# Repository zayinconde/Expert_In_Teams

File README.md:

This is my expert and teams electronics repository. The project is a multi-dsiciplinary project. This repository contains all the files related to the electronics part by me (Zayin Conde). 

The embedded software is developed in VS code using platformio cross platform developemnt tool. 

The repository also contains the KICAD files for circuit schematics and PCB designs. 

Additionally, a project B.O.M list is linked along with a brainstorming document (note: language can be informal, used for personal brainstorming and decision making) (View only with SDU Mail)

[📄 View the live Brainstorming Document (Word)](https://syddanskuni.sharepoint.com/:w:/s/AIDeputyExpertinTeams/ETyJX5G7IEFBnaOn01ZgCaMBbD81jJfqN7rkElq9ijI7jw?e=0cWUlB)
[📊 View the live B.O.M list (Excel)](https://syddanskuni.sharepoint.com/:x:/s/AIDeputyExpertinTeams/EaCTvVSukcdOoP5wCQjI0uoB_z5LuD4u5wMGKWqrb4GMKw?e=0rVpbN)

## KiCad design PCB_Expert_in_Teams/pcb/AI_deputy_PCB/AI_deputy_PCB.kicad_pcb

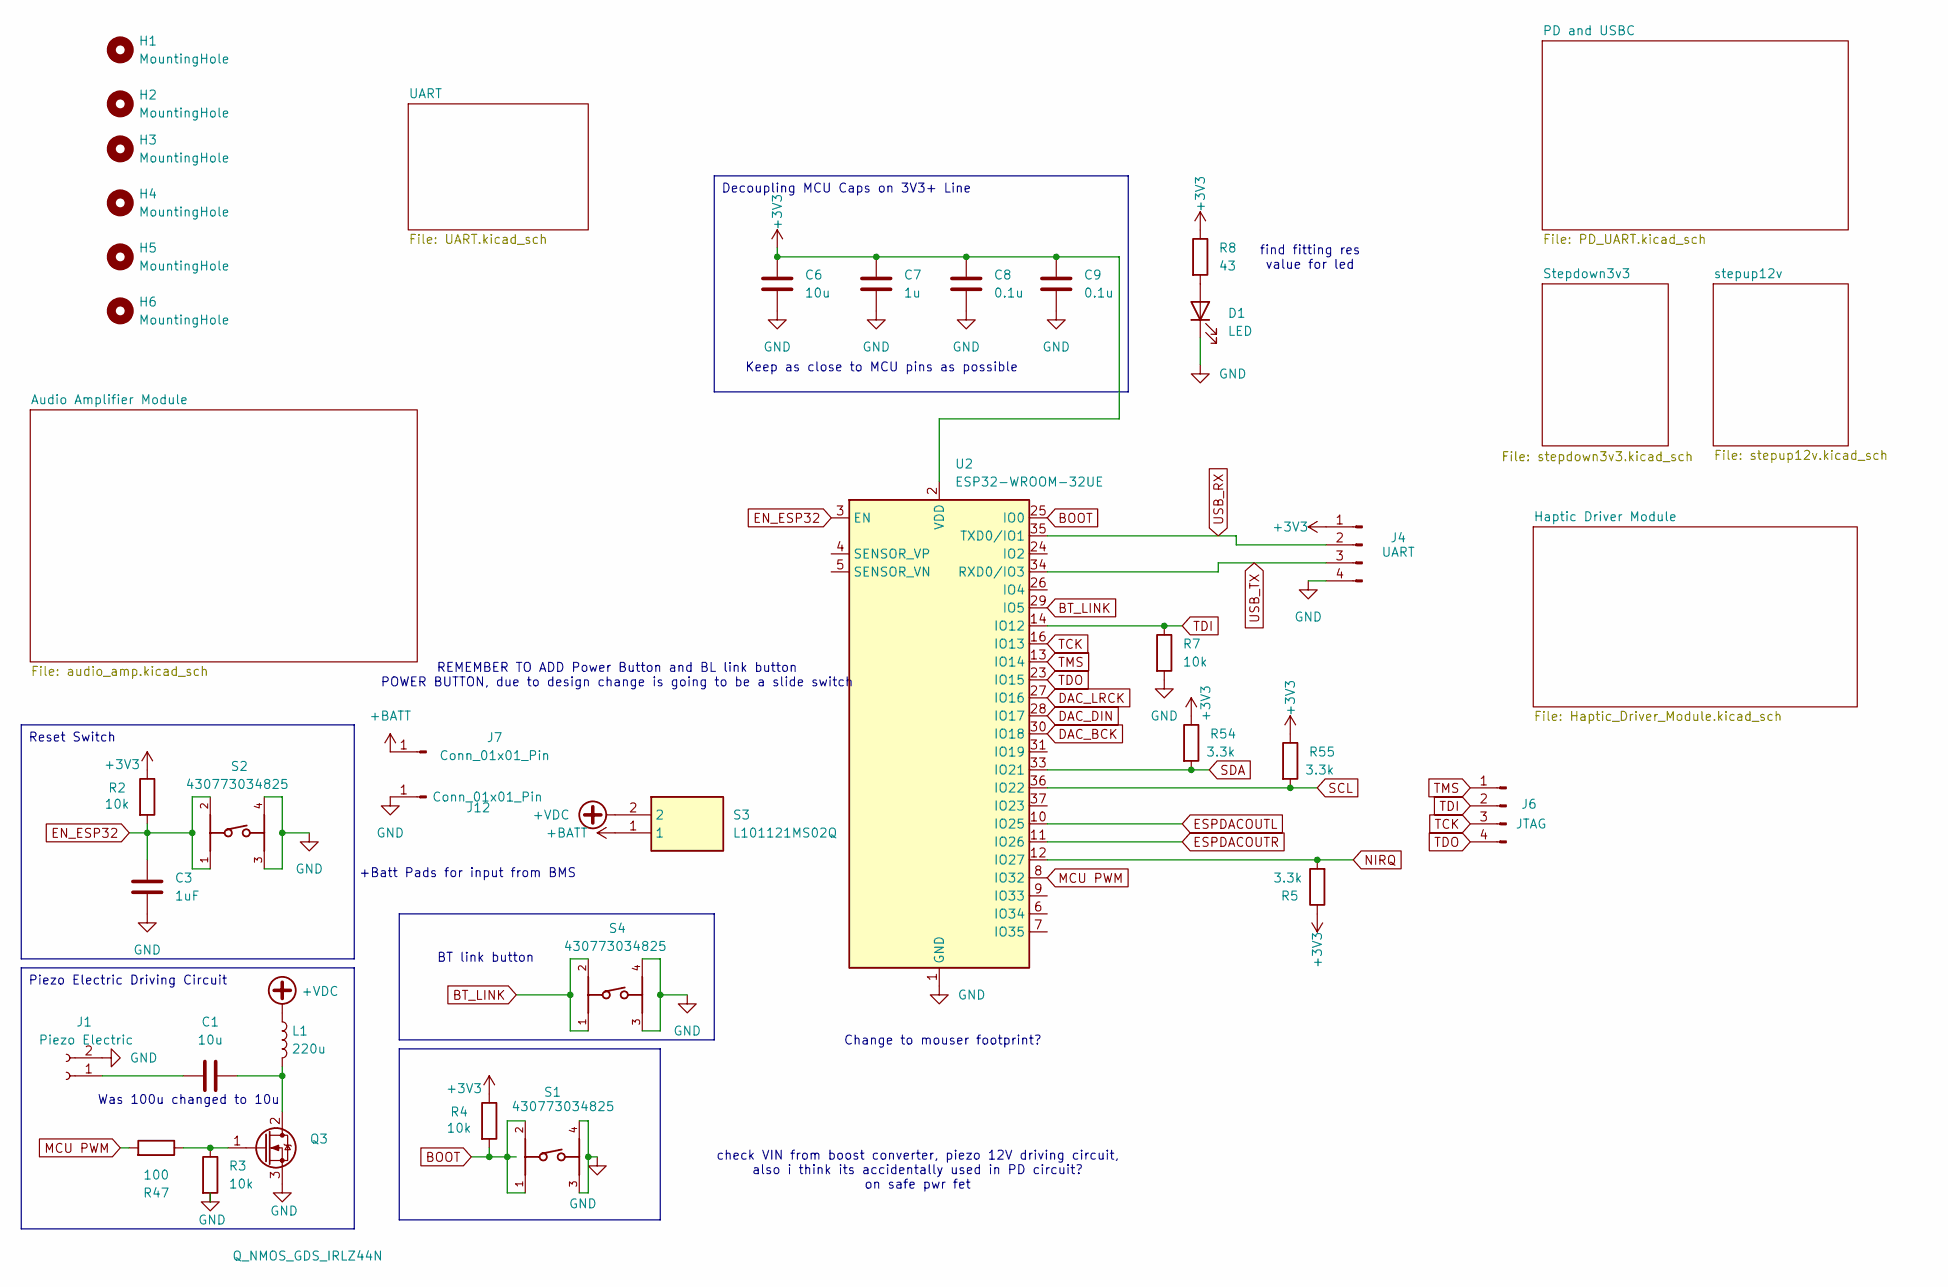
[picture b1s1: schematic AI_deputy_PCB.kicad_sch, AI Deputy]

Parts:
C1, C6: 10u; C_0805_2012Metric_Pad1.18x1.45mm_HandSolder
C3: 1uF; C_0805_2012Metric_Pad1.18x1.45mm_HandSolder
C7: 1u; C_0805_2012Metric_Pad1.18x1.45mm_HandSolder
C8, C9: 0.1u; C_0805_2012Metric_Pad1.18x1.45mm_HandSolder
D1: LED; LED_0805_2012Metric_Pad1.15x1.40mm_HandSolder
H1, H2, H3, H4, H5, H6: MountingHole; MountingHole_3mm
J1: Piezo Electric; JST_XH_S2B-XH-A-1_1x02_P2.50mm_Horizontal
J4: UART; PinHeader_1x04_P2.54mm_Vertical
J6: JTAG; PinHeader_1x04_P2.54mm_Vertical
J7, J12: Conn_01x01_Pin; TestPoint_Pad_4.0x4.0mm
L1: 220u; L_Wuerth_WE-PD-Typ-LS
Q3: Q_NMOS_GDS_IRLZ44N; TO-220-3_Horizontal_TabDown
R2, R3, R4, R7: 10k; R_0805_2012Metric_Pad1.20x1.40mm_HandSolder
R5, R54, R55: 3.3k; R_0805_2012Metric_Pad1.20x1.40mm_HandSolder
R8: 43; R_0805_2012Metric_Pad1.20x1.40mm_HandSolder
R47: 100; R_0805_2012Metric_Pad1.20x1.40mm_HandSolder
S1, S2, S4: 430773034825
S3: L101121MS02Q; PWR_SW_L101021MS02Q; Mouser Part Number 611-L101121MS02Q
U2: ESP32-WROOM-32UE

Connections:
+3V3: C6.1, C7.1, C8.1, C9.2, J4.1, R2.1, R4.1, R5.1, R8.1, R54.1, R55.1, U2.2 (VDD); also elsewhere on the board
+BATT: J7.1, S3.1
+VDC: L1.1, S3.2; also elsewhere on the board
BOOT: R4.2, S1.1, S1.2, U2.25 (IO0)
BT_LINK: S4.1, S4.2, U2.29 (IO5)
DAC_BCK: U2.30 (IO18); also elsewhere on the board
DAC_DIN: U2.28 (IO17); also elsewhere on the board
DAC_LRCK: U2.27 (IO16); also elsewhere on the board
EN_ESP32: C3.1, R2.2, S2.1, S2.2, U2.3 (EN)
ESPDACOUTL: U2.10 (IO25); also elsewhere on the board
ESPDACOUTR: U2.11 (IO26); also elsewhere on the board
GND: C3.2, C6.2, C7.2, C8.2, C9.1, D1.1 (K), J1.2, J4.4, J12.1, Q3.3 (S), R3.2, R7.2, S1.3, S1.4, S2.3, S2.4, S4.3, S4.4, U2.1 (GND), U2.15 (GND), U2.38 (GND), U2.39 (GND); also elsewhere on the board
MCU PWM: R47.2, U2.8 (IO32)
NIRQ: R5.2, U2.12 (IO27); also elsewhere on the board
unnamed: D1.2 (A), R8.2
unnamed: C1.1, J1.1
unnamed: C1.2, L1.2, Q3.2 (D)
unnamed: Q3.1 (G), R3.1, R47.1
SCL: R55.2, U2.36 (IO22); also elsewhere on the board
SDA: R54.2, U2.33 (IO21); also elsewhere on the board
TCK: J6.3, U2.16 (IO13)
TDI: J6.2, R7.1, U2.14 (IO12)
TDO: J6.4, U2.23 (IO15)
TMS: J6.1, U2.13 (IO14)
USB_RX: J4.2, U2.35 (TXD0/IO1); also elsewhere on the board
USB_TX: J4.3, U2.34 (RXD0/IO3); also elsewhere on the board

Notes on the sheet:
Keep as close to MCU pins as possible
Was 100u changed to 10u
BT link button
REMEMBER TO ADD Power Button and BL link button POWER BUTTON, due to design change is going to be a slide switch
+Batt Pads for input from BMS
find fitting res value for led
check VIN from boost converter, piezo 12V driving circuit, also i think its accidentally used in PD circuit? on safe pwr fet
Change to mouser footprint?
Piezo Electric Driving Circuit
Decoupling MCU Caps on 3V3+ Line
Reset Switch

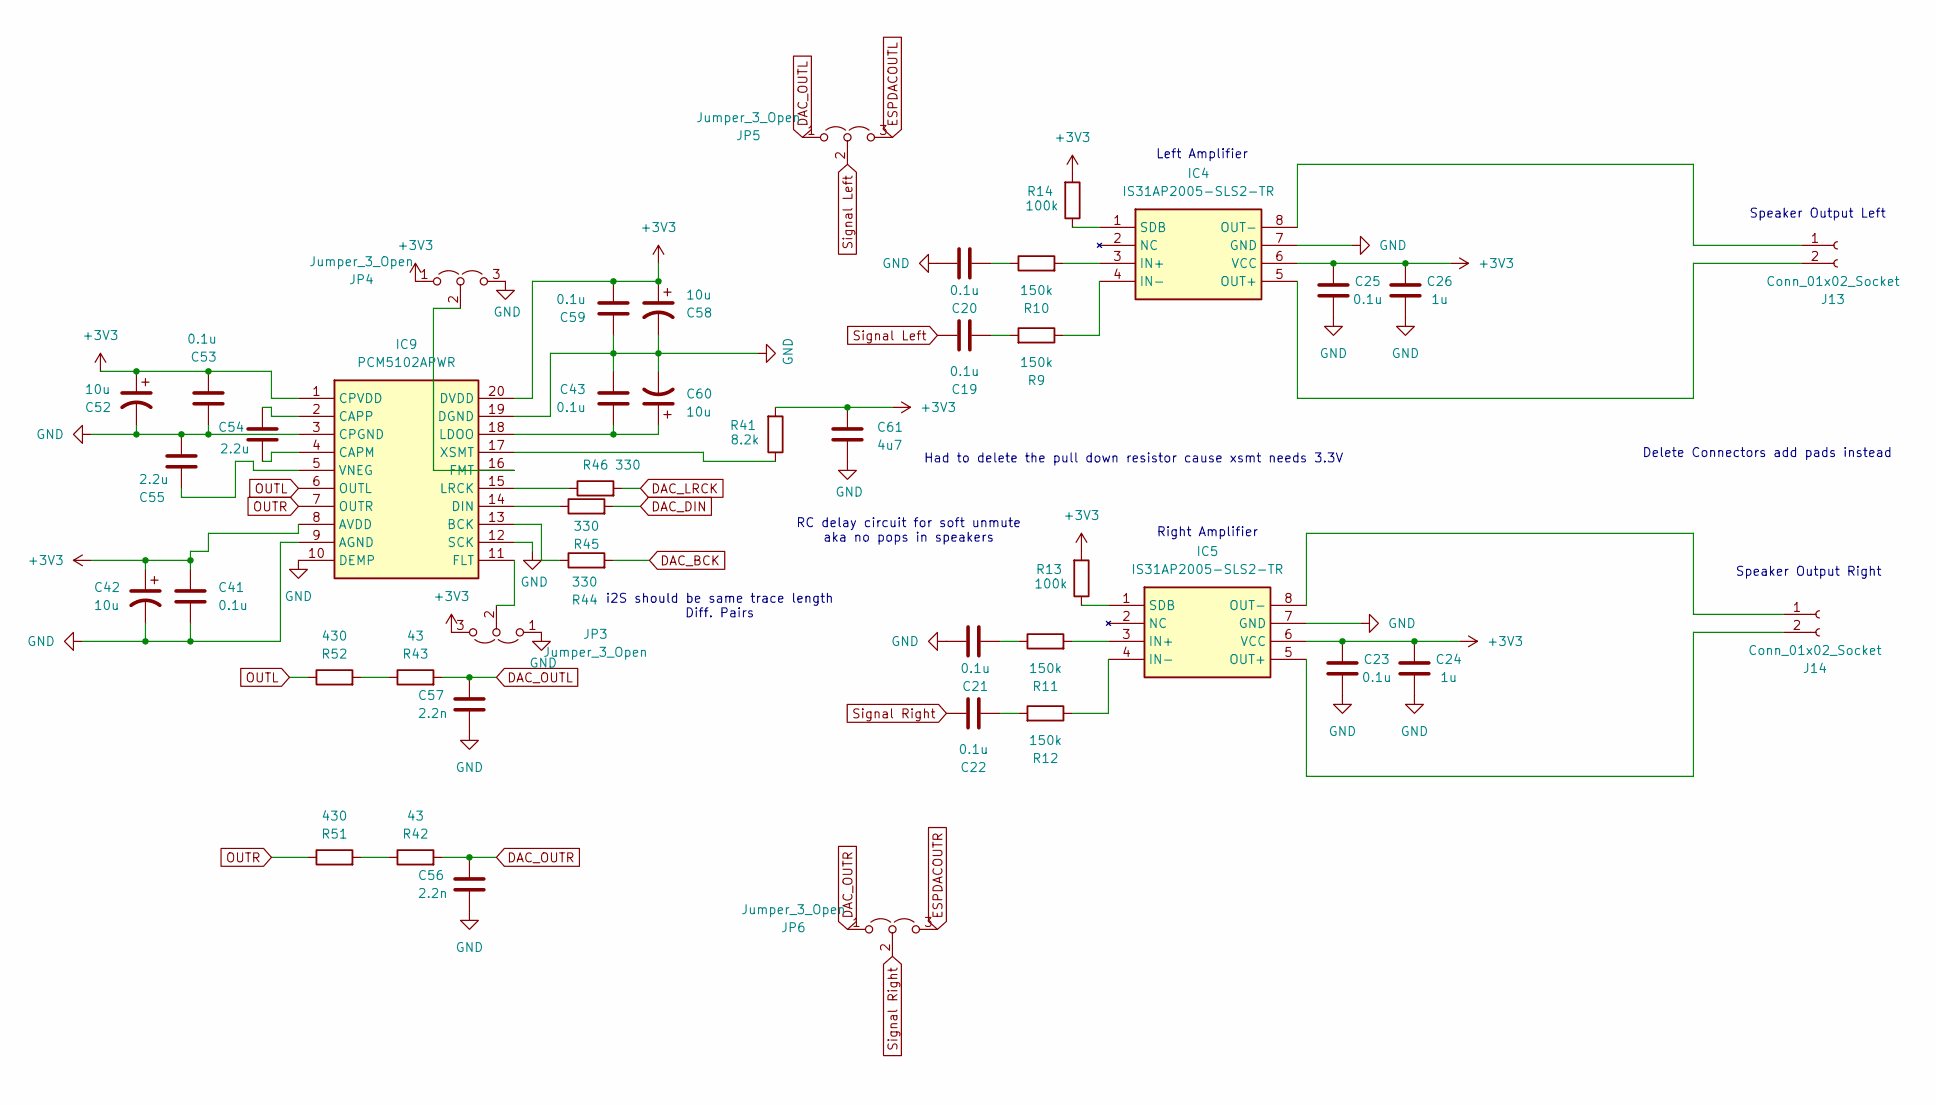
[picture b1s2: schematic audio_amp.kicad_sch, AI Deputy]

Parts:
C19, C20, C21, C22, C23, C25, C41, C43, C53, C59: 0.1u; C_0805_2012Metric_Pad1.18x1.45mm_HandSolder
C24, C26: 1u; C_0805_2012Metric_Pad1.18x1.45mm_HandSolder
C42, C52, C58, C60: 10u; CP_Elec_4x5.4
C54, C55: 2.2u; C_0805_2012Metric_Pad1.18x1.45mm_HandSolder
C56, C57: 2.2n; C_0201_0603Metric_Pad0.64x0.40mm_HandSolder
C61: 4u7; C_0805_2012Metric_Pad1.18x1.45mm_HandSolder
IC4, IC5: IS31AP2005-SLS2-TR; SOP65P490X110-8N; Manufacturer_Part_Number IS31AP2005-SLS2-TR
IC9: PCM5102APWR; SOP65P640X120-20N; Mouser Part Number 595-PCM5102APWR
J13, J14: Conn_01x02_Socket; JST_XH_S2B-XH-A-1_1x02_P2.50mm_Horizontal
JP3, JP4, JP5, JP6: Jumper_3_Open; SolderJumper-3_P1.3mm_Open_Pad1.0x1.5mm_NumberLabels
R9, R10, R11, R12: 150k; R_0805_2012Metric_Pad1.20x1.40mm_HandSolder
R13, R14: 100k; R_0805_2012Metric_Pad1.20x1.40mm_HandSolder
R41: 8.2k; R_0805_2012Metric_Pad1.20x1.40mm_HandSolder
R42, R43: 43; R_0805_2012Metric_Pad1.20x1.40mm_HandSolder
R44, R45, R46: 330; R_0805_2012Metric_Pad1.20x1.40mm_HandSolder
R51, R52: 430; R_0805_2012Metric_Pad1.20x1.40mm_HandSolder

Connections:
+3V3: C23.2, C24.2, C25.2, C26.2, C41.1, C42.1, C52.1, C53.2, C58.1, C59.2, C61.1, IC4.6 (VCC), IC5.6 (VCC), IC9.1 (CPVDD), IC9.8 (AVDD), IC9.20 (DVDD), JP3.3 (B), JP4.1 (A), R13.2, R14.2, R41.2; also elsewhere on the board
DAC_BCK: R44.2; also elsewhere on the board
DAC_DIN: R45.2; also elsewhere on the board
DAC_LRCK: R46.2; also elsewhere on the board
DAC_OUTL: C57.1, JP5.1 (A), R43.2
DAC_OUTR: C56.1, JP6.1 (A), R42.2
ESPDACOUTL: JP5.3 (B); also elsewhere on the board
ESPDACOUTR: JP6.3 (B); also elsewhere on the board
GND: C20.1, C21.1, C23.1, C24.1, C25.1, C26.1, C41.2, C42.2, C43.1, C52.2, C53.1, C55.1, C56.2, C57.2, C58.2, C59.1, C60.2, C61.2, IC4.7 (GND), IC5.7 (GND), IC9.3 (CPGND), IC9.9 (AGND), IC9.10 (DEMP), IC9.12 (SCK), IC9.19 (DGND), JP3.1 (A), JP4.3 (B); also elsewhere on the board
unnamed: C19.2, R9.2
unnamed: C20.2, R10.1
unnamed: C21.2, R11.1
unnamed: C22.2, R12.2
unnamed: IC4.3 (IN+), R10.2
unnamed: IC4.4 (IN-), R9.1
unnamed: IC4.5 (OUT+), J13.2
unnamed: IC4.8 (OUT-), J13.1
unnamed: IC4.1 (SDB), R14.1
unnamed: IC5.3 (IN+), R11.2
unnamed: IC5.4 (IN-), R12.1
unnamed: IC5.5 (OUT+), J14.2
unnamed: IC5.8 (OUT-), J14.1
unnamed: IC5.1 (SDB), R13.1
unnamed: IC9.13 (BCK), R44.1
unnamed: C54.2, IC9.4 (CAPM)
unnamed: C54.1, IC9.2 (CAPP)
unnamed: IC9.14 (DIN), R45.1
unnamed: IC9.11 (FLT), JP3.2 (C)
unnamed: IC9.16 (FMT), JP4.2 (C)
unnamed: C43.2, C60.1, IC9.18 (LDOO)
unnamed: IC9.15 (LRCK), R46.1
unnamed: C55.2, IC9.5 (VNEG)
unnamed 74: IC9.17 (XSMT), R41.1; also elsewhere on the board
unnamed: R42.1, R51.2
unnamed: R43.1, R52.2
OUTL: IC9.6 (OUTL), R52.1
OUTR: IC9.7 (OUTR), R51.1
Signal Left: C19.1, JP5.2 (C)
Signal Right: C22.1, JP6.2 (C)

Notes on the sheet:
Speaker Output Right
Delete Connectors add pads instead
Speaker Output Left
RC delay circuit for soft unmute aka no pops in speakers
Left Amplifier
i2S should be same trace length Diff. Pairs
Right Amplifier
Had to delete the pull down resistor cause xsmt needs 3.3V

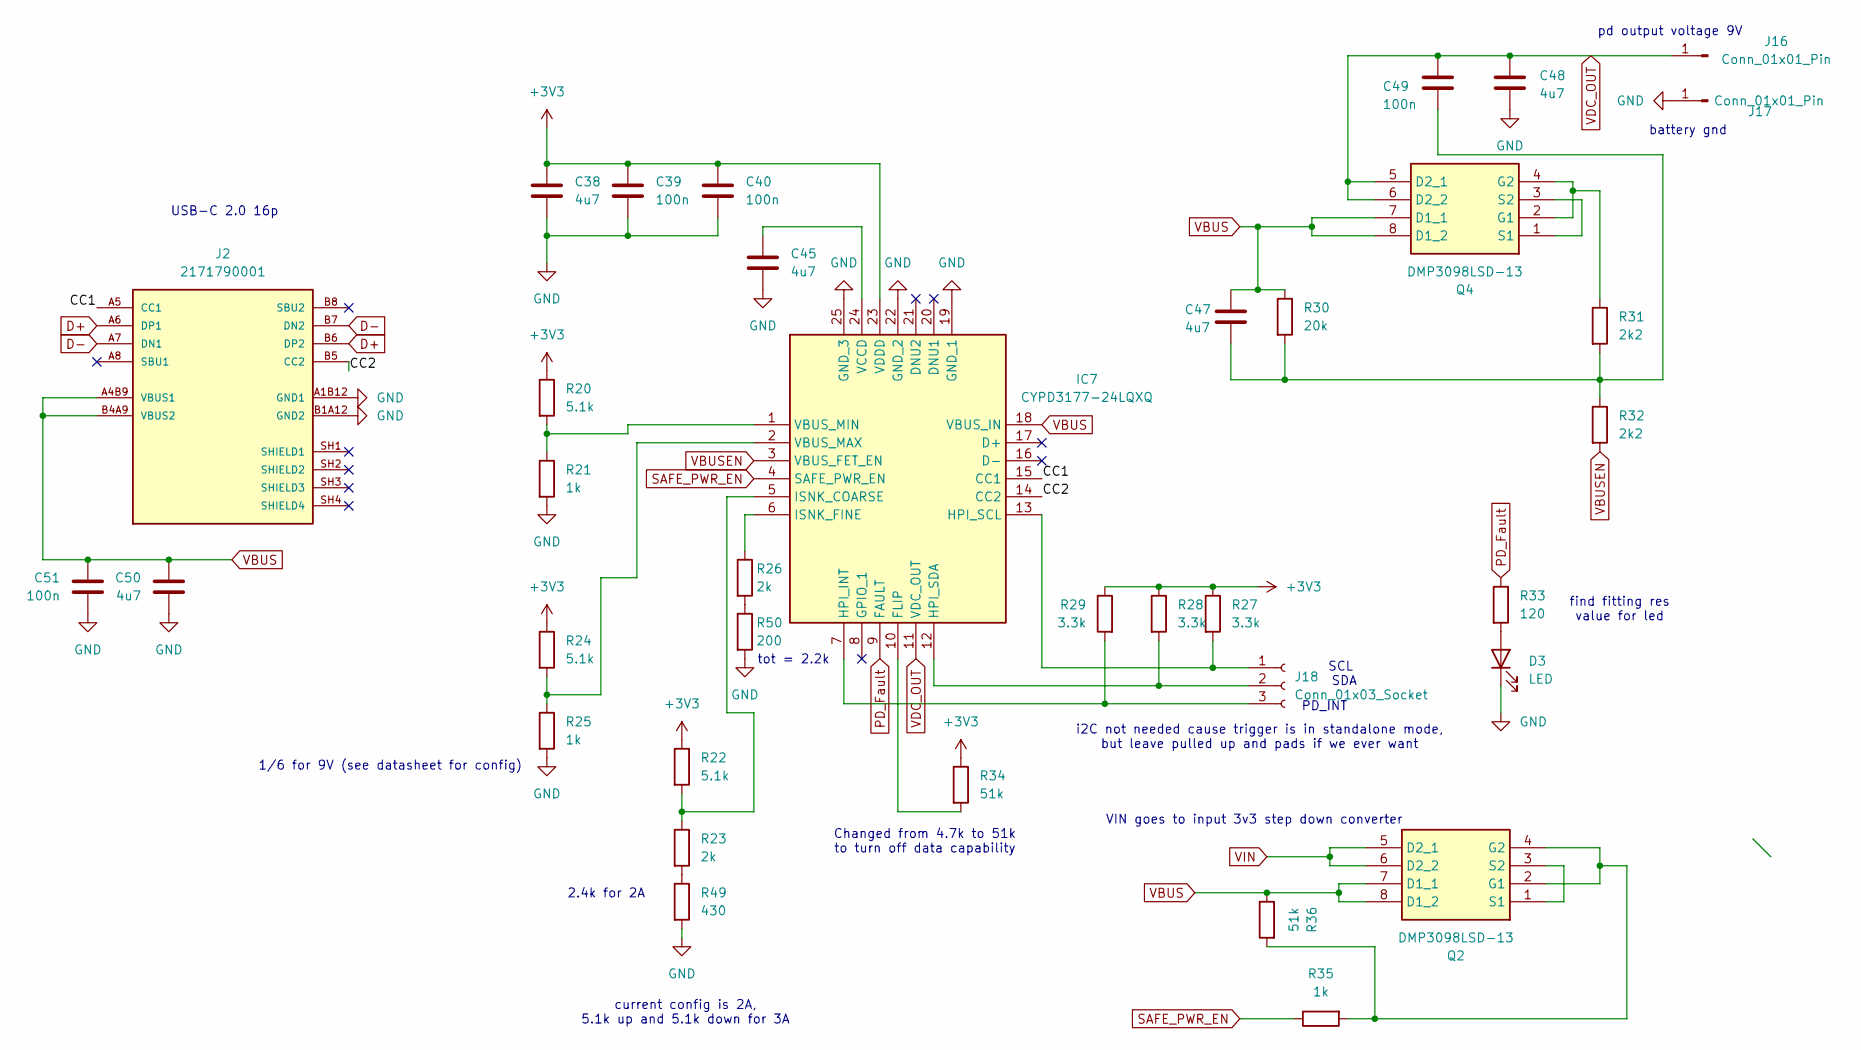
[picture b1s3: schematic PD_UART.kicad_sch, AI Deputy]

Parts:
C38, C45, C47, C48, C50: 4u7; C_0805_2012Metric_Pad1.18x1.45mm_HandSolder
C39, C40, C49, C51: 100n; C_0805_2012Metric_Pad1.18x1.45mm_HandSolder
D3: LED; LED_0805_2012Metric_Pad1.15x1.40mm_HandSolder
IC7: CYPD3177-24LQXQ; QFN50P400X400X60-25N-D; Mouser Part Number 727-CYPD3177-24LQXQ
J2: 2171790001; MOLEX_2171790001; PARTREV A1
J16, J17: Conn_01x01_Pin; TestPoint_Pad_4.0x4.0mm
J18: Conn_01x03_Socket; PinHeader_1x03_P2.54mm_Vertical
Q2, Q4: DMP3098LSD-13; SOIC127P600X175-8N; Mouser Part Number 621-DMP3098LSD-13
R20, R22, R24: 5.1k; R_0805_2012Metric_Pad1.20x1.40mm_HandSolder
R21, R25, R35: 1k; R_0805_2012Metric_Pad1.20x1.40mm_HandSolder
R23, R26: 2k; R_0805_2012Metric_Pad1.20x1.40mm_HandSolder
R27, R28, R29: 3.3k; R_0805_2012Metric_Pad1.20x1.40mm_HandSolder
R30: 20k; R_0805_2012Metric_Pad1.20x1.40mm_HandSolder
R31, R32: 2k2; R_0805_2012Metric_Pad1.20x1.40mm_HandSolder
R33: 120; R_0805_2012Metric_Pad1.20x1.40mm_HandSolder
R34, R36: 51k; R_0805_2012Metric_Pad1.20x1.40mm_HandSolder
R49: 430; R_0805_2012Metric_Pad1.20x1.40mm_HandSolder
R50: 200; R_0805_2012Metric_Pad1.20x1.40mm_HandSolder

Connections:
+3V3: C38.1, C39.1, C40.1, IC7.23 (VDDD), R20.1, R22.1, R24.1, R27.1, R28.1, R29.1, R34.1; also elsewhere on the board
/PD and USBC/CC1: IC7.15 (CC1), J2.A5 (CC1)
/PD and USBC/CC2: IC7.14 (CC2), J2.B5 (CC2)
D+: J2.A6 (DP1), J2.B6 (DP2); also elsewhere on the board
D-: J2.A7 (DN1), J2.B7 (DN2); also elsewhere on the board
GND: C38.2, C39.2, C40.2, C45.2, C48.2, C50.2, C51.2, D3.1 (K), IC7.19 (GND_1), IC7.22 (GND_2), IC7.25 (GND_3), J2.A1B12 (GND1), J2.B1A12 (GND2), J17.1, R21.2, R25.2, R49.2, R50.2; also elsewhere on the board
unnamed: C47.2, C49.2, R30.2, R31.2, R32.1
unnamed: D3.2 (A), R33.2
unnamed: IC7.10 (FLIP), R34.2
unnamed: IC7.7 (HPI_INT), J18.3, R29.2
unnamed: IC7.13 (HPI_SCL), J18.1, R27.2
unnamed: IC7.12 (HPI_SDA), J18.2, R28.2
unnamed: IC7.5 (ISNK_COARSE), R22.2, R23.1
unnamed: IC7.6 (ISNK_FINE), R26.1
unnamed: IC7.2 (VBUS_MAX), R24.2, R25.1
unnamed: IC7.1 (VBUS_MIN), R20.2, R21.1
unnamed: C45.1, IC7.24 (VCCD)
unnamed: Q2.2 (G1), Q2.4 (G2), R35.2, R36.2
unnamed: Q2.1 (S1), Q2.3 (S2)
unnamed: Q4.2 (G1), Q4.4 (G2), R31.1
unnamed: Q4.1 (S1), Q4.3 (S2)
unnamed: R23.2, R49.1
unnamed: R26.2, R50.1
PD_Fault: IC7.9 (FAULT), R33.1
SAFE_PWR_EN: IC7.4 (SAFE_PWR_EN), R35.1
VBUS: C47.1, C50.1, C51.1, IC7.18 (VBUS_IN), J2.A4B9 (VBUS1), J2.B4A9 (VBUS2), Q2.7 (D1_1), Q2.8 (D1_2), Q4.7 (D1_1), Q4.8 (D1_2), R30.1, R36.1
VBUSEN: IC7.3 (VBUS_FET_EN), R32.2
VDC_OUT: C48.1, C49.1, IC7.11 (VDC_OUT), J16.1, Q4.5 (D2_1), Q4.6 (D2_2)
VIN: Q2.5 (D2_1), Q2.6 (D2_2)

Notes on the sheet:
i2C not needed cause trigger is in standalone mode, but leave pulled up and pads if we ever want
Changed from 4.7k to 51k to turn off data capability
find fitting res value for led
SDA
current config is 2A, 5.1k up and 5.1k down for 3A
SCL
USB-C 2.0 16p
VIN goes to input 3v3 step down converter
PD_INT
battery gnd
pd output voltage 9V
tot = 2.2k
1/6 for 9V (see datasheet for config)
2.4k for 2A

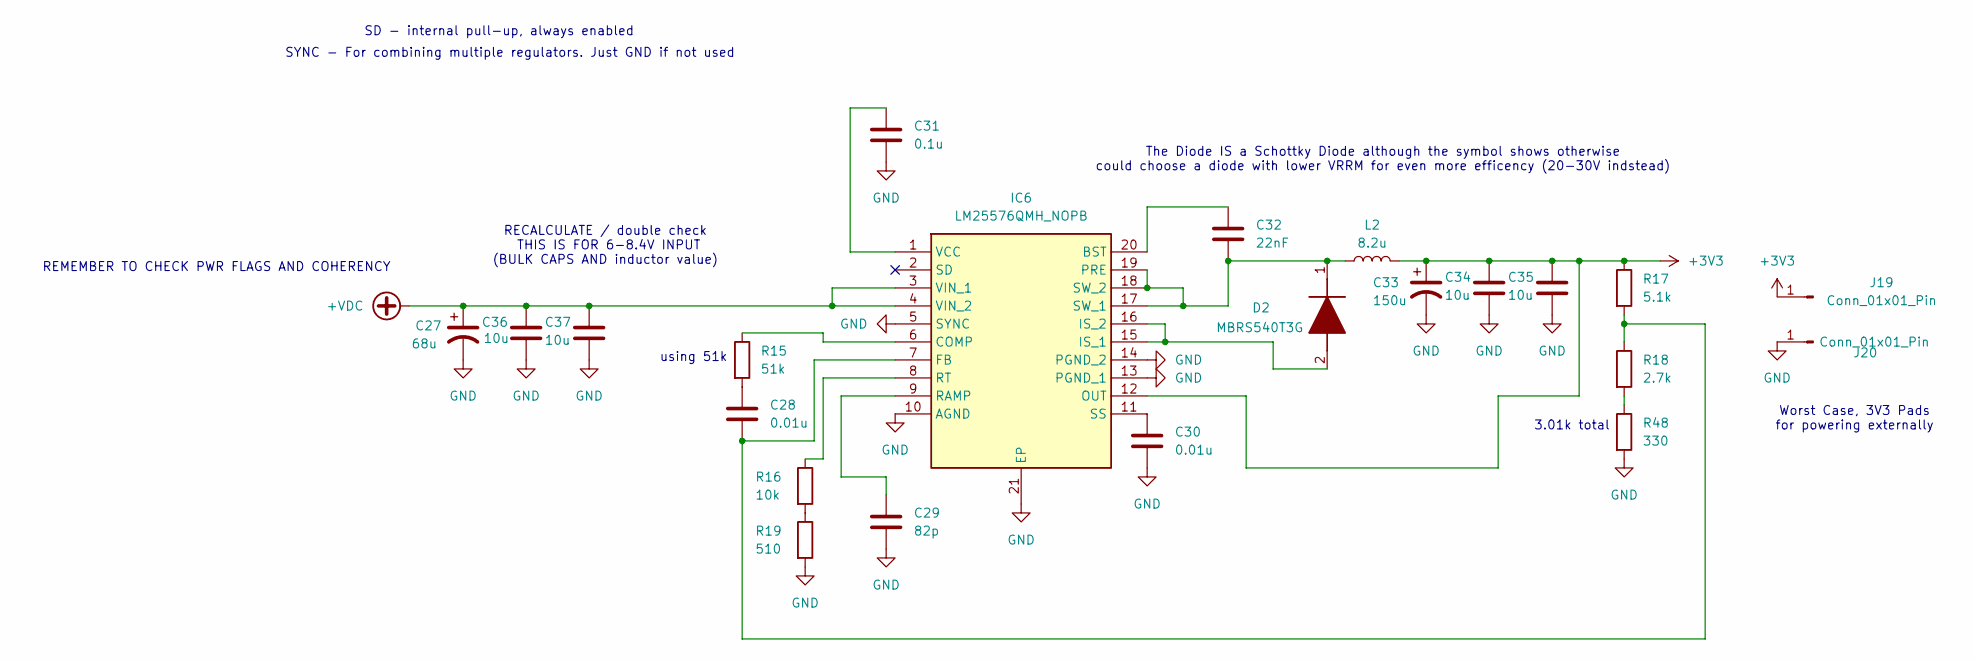
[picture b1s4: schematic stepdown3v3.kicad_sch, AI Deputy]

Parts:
C27: 68u; T520D
C28, C30: 0.01u; C_0805_2012Metric_Pad1.18x1.45mm_HandSolder
C29: 82p; C_0805_2012Metric_Pad1.18x1.45mm_HandSolder
C31: 0.1u; C_0805_2012Metric_Pad1.18x1.45mm_HandSolder
C32: 22nF; C_0805_2012Metric_Pad1.18x1.45mm_HandSolder
C33: 150u; SX_Package
C34, C35, C36, C37: 10u; C_0805_2012Metric_Pad1.18x1.45mm_HandSolder
D2: MBRS540T3G; DIOM7958X256N; Manufacturer_Part_Number MBRS540T3G
IC6: LM25576QMH_NOPB; SOP65P640X110-21N; Mouser Part Number 926-LM25576QMH/NOPB
J19, J20: Conn_01x01_Pin; TestPoint_Pad_4.0x4.0mm
L2: 8.2u; INDPM7166X300N
R15: 51k; R_0805_2012Metric_Pad1.20x1.40mm_HandSolder
R16: 10k; R_0805_2012Metric_Pad1.20x1.40mm_HandSolder
R17: 5.1k; R_0805_2012Metric_Pad1.20x1.40mm_HandSolder
R18: 2.7k; R_0805_2012Metric_Pad1.20x1.40mm_HandSolder
R19: 510; R_0805_2012Metric_Pad1.20x1.40mm_HandSolder
R48: 330; R_0805_2012Metric_Pad1.20x1.40mm_HandSolder

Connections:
+3V3: C33.1, C34.1, C35.1, IC6.12 (OUT), J19.1, L2.2, R17.1; also elsewhere on the board
+VDC: C27.1, C36.1, C37.1, IC6.3 (VIN_1), IC6.4 (VIN_2); also elsewhere on the board
GND: C27.2, C29.2, C30.2, C31.2, C33.2, C34.2, C35.2, C36.2, C37.2, IC6.5 (SYNC), IC6.10 (AGND), IC6.13 (PGND_1), IC6.14 (PGND_2), IC6.21 (EP), J20.1, R19.2, R48.2; also elsewhere on the board
unnamed: C28.1, R15.2
unnamed: D2.2 (A), IC6.15 (IS_1), IC6.16 (IS_2)
unnamed: C32.2, D2.1 (K), IC6.17 (SW_1), IC6.18 (SW_2), IC6.19 (PRE), L2.1
unnamed: C32.1, IC6.20 (BST)
unnamed: IC6.6 (COMP), R15.1
unnamed: C28.2, IC6.7 (FB), R17.2, R18.1
unnamed: C29.1, IC6.9 (RAMP)
unnamed: IC6.8 (RT), R16.1
unnamed: C30.1, IC6.11 (SS)
unnamed: C31.1, IC6.1 (VCC)
unnamed: R16.2, R19.1
unnamed: R18.2, R48.1

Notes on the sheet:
RECALCULATE / double check THIS IS FOR 6-8.4V INPUT (BULK CAPS AND inductor value)
SYNC - For combining multiple regulators. Just GND if not used
3.01k total
using 51k
SD - internal pull-up, always enabled
Worst Case, 3V3 Pads for powering externally
REMEMBER TO CHECK PWR FLAGS AND COHERENCY
The Diode IS a Schottky Diode although the symbol shows otherwise could choose a diode with lower VRRM for even more efficency (20-30V indstead)

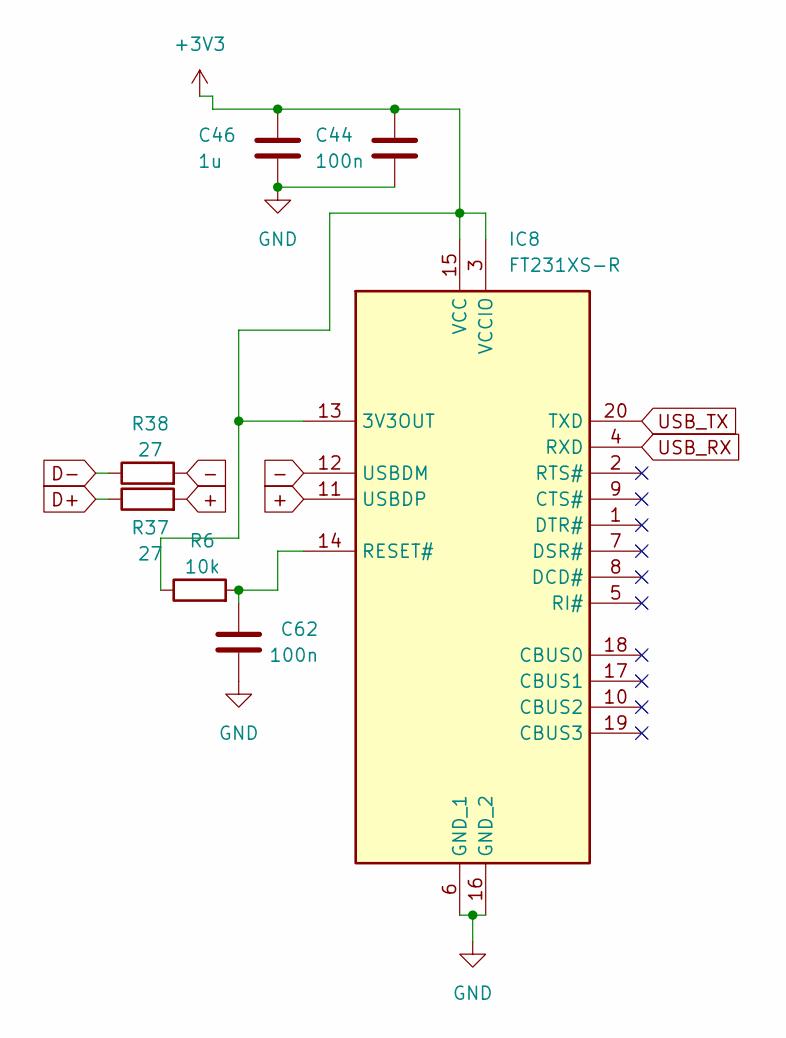
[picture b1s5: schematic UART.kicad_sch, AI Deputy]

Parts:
C44, C62: 100n; C_0805_2012Metric_Pad1.18x1.45mm_HandSolder
C46: 1u; C_0805_2012Metric_Pad1.18x1.45mm_HandSolder
IC8: FT231XS-R; SOP64P599X175-20N; Mouser Part Number 895-FT231XS-R
R6: 10k; R_0805_2012Metric_Pad1.20x1.40mm_HandSolder
R37, R38: 27; R_0805_2012Metric_Pad1.20x1.40mm_HandSolder

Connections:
+: IC8.11 (USBDP), R37.2
+3V3: C44.1, C46.1, IC8.3 (VCCIO), IC8.13 (3V3OUT), IC8.15 (VCC), R6.1; also elsewhere on the board
-: IC8.12 (USBDM), R38.2
D+: R37.1; also elsewhere on the board
D-: R38.1; also elsewhere on the board
GND: C44.2, C46.2, C62.2, IC8.6 (GND_1), IC8.16 (GND_2); also elsewhere on the board
unnamed: C62.1, IC8.14 (RESET#), R6.2
USB_RX: IC8.4 (RXD); also elsewhere on the board
USB_TX: IC8.20 (TXD); also elsewhere on the board

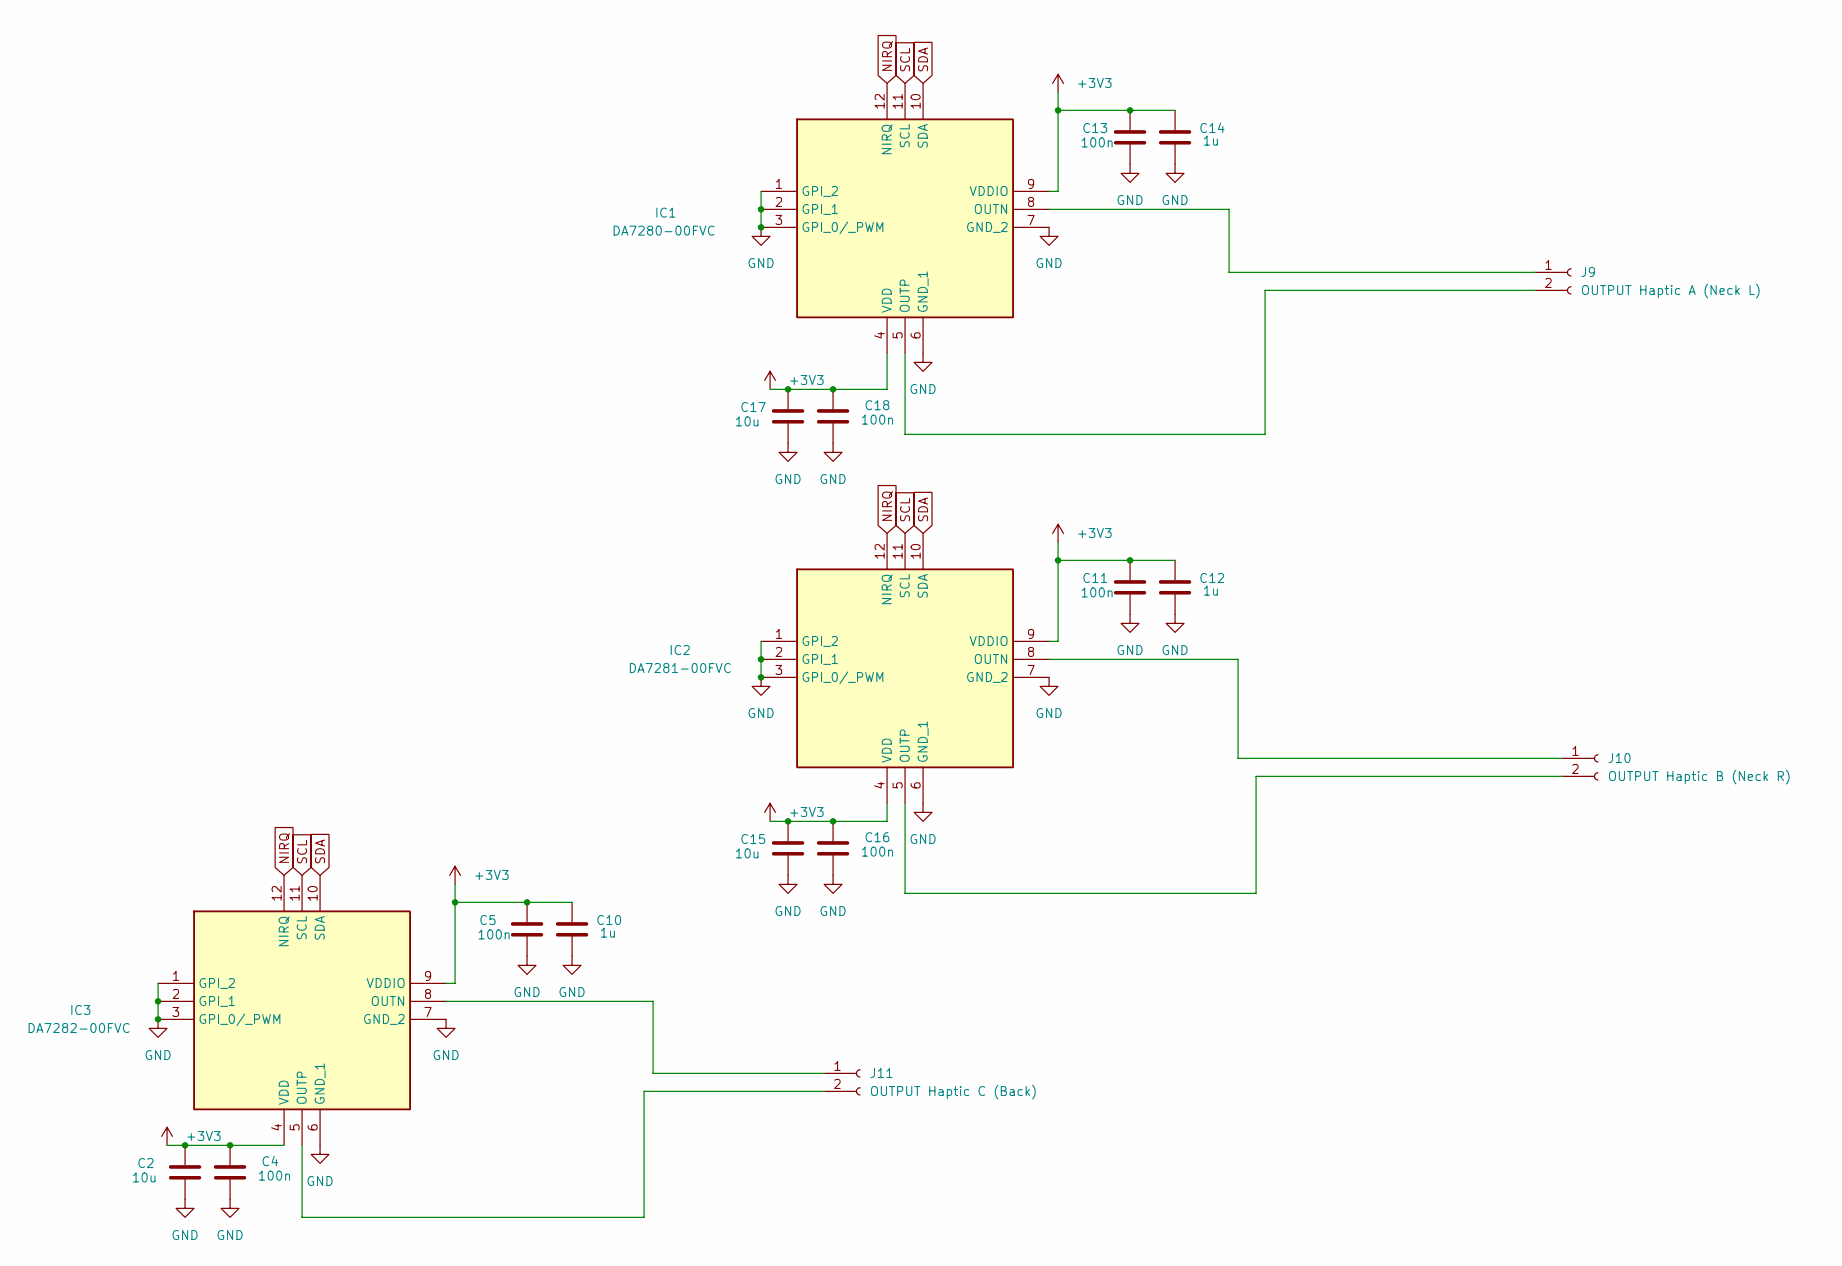
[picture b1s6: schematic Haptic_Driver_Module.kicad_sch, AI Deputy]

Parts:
C2, C15, C17: 10u; C_0805_2012Metric_Pad1.18x1.45mm_HandSolder
C4, C5, C11, C13, C16, C18: 100n; C_0805_2012Metric_Pad1.18x1.45mm_HandSolder
C10, C12, C14: 1u; C_0805_2012Metric_Pad1.18x1.45mm_HandSolder
IC1: DA7280-00FVC; QFN65P300X300X84-12N; Manufacturer_Part_Number DA7280-00FVC
IC2: DA7281-00FVC; QFN65P300X300X84-12N; Manufacturer_Part_Number DA7280-00FVC
IC3: DA7282-00FVC; QFN65P300X300X84-12N; Manufacturer_Part_Number DA7280-00FVC
J9: OUTPUT Haptic A (Neck L); JST_XH_S2B-XH-A_1x02_P2.50mm_Horizontal
J10: OUTPUT Haptic B (Neck R); JST_XH_S2B-XH-A_1x02_P2.50mm_Horizontal
J11: OUTPUT Haptic C (Back); JST_XH_S2B-XH-A_1x02_P2.50mm_Horizontal

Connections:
+3V3: C2.1, C4.1, C5.1, C10.1, C11.1, C12.1, C13.1, C14.1, C15.1, C16.1, C17.1, C18.1, IC1.4 (VDD), IC1.9 (VDDIO), IC2.4 (VDD), IC2.9 (VDDIO), IC3.4 (VDD), IC3.9 (VDDIO); also elsewhere on the board
GND: C2.2, C4.2, C5.2, C10.2, C11.2, C12.2, C13.2, C14.2, C15.2, C16.2, C17.2, C18.2, IC1.1 (GPI_2), IC1.2 (GPI_1), IC1.3 (GPI_0/_PWM), IC1.6 (GND_1), IC1.7 (GND_2), IC2.1 (GPI_2), IC2.2 (GPI_1), IC2.3 (GPI_0/_PWM), IC2.6 (GND_1), IC2.7 (GND_2), IC3.1 (GPI_2), IC3.2 (GPI_1), IC3.3 (GPI_0/_PWM), IC3.6 (GND_1), IC3.7 (GND_2); also elsewhere on the board
NIRQ: IC1.12 (NIRQ), IC2.12 (NIRQ), IC3.12 (NIRQ); also elsewhere on the board
unnamed: IC1.8 (OUTN), J9.1
unnamed: IC1.5 (OUTP), J9.2
unnamed: IC2.8 (OUTN), J10.1
unnamed: IC2.5 (OUTP), J10.2
unnamed: IC3.8 (OUTN), J11.1
unnamed: IC3.5 (OUTP), J11.2
SCL: IC1.11 (SCL), IC2.11 (SCL), IC3.11 (SCL); also elsewhere on the board
SDA: IC1.10 (SDA), IC2.10 (SDA), IC3.10 (SDA); also elsewhere on the board

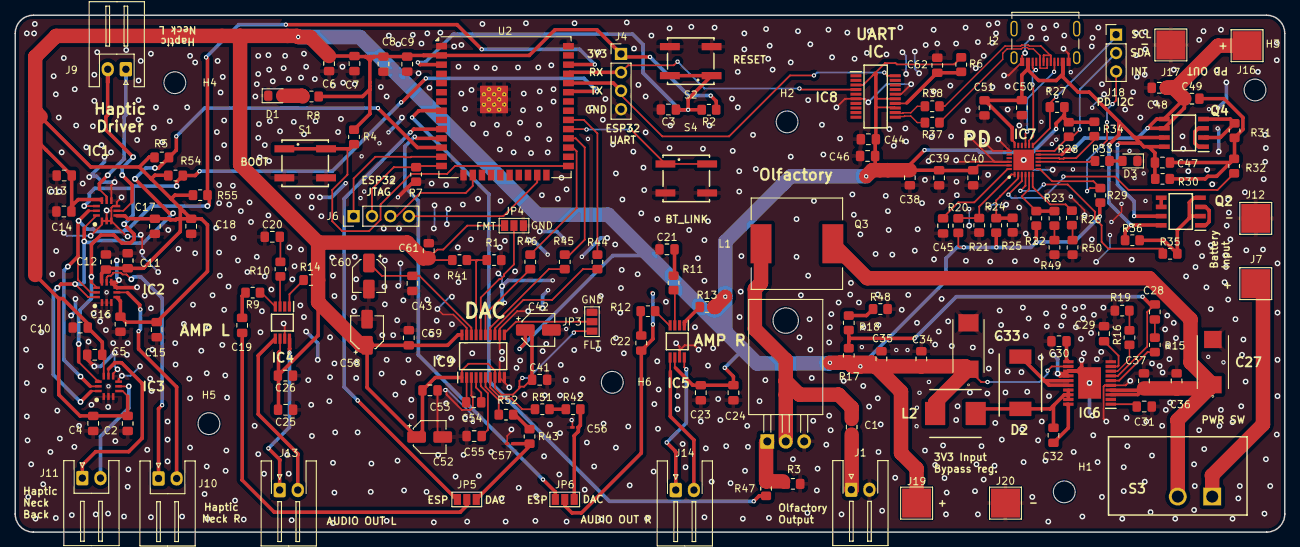
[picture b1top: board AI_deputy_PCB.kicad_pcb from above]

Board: 2 copper layers, 175.0 x 71.2 mm, 162 parts (0 on the bottom side), 106 nets.

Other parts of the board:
R1: 2.7k; R_0805_2012Metric_Pad1.20x1.40mm_HandSolder

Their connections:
GND: R1.1; also elsewhere on the board
unnamed 74: R1.2; also elsewhere on the board

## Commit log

2025-10-28 commit including files test
2025-10-28 moving embedded in
2025-10-28 pushing all laptop files so repo is up to date
2025-10-28 Update README with project description and resources
    Added project overview and details about tools used.
2025-10-28 updating repo from desktop
2025-10-28 Update README with project report and results links
    Added links to the latest project report and results spreadsheet.
2025-10-28 Fix formatting issues in README.md
2025-10-28 Update README with live document links
    Updated links to point to live documents instead of latest versions.
2025-10-28 progress on PCB + matlab calculations
2025-10-30 29/10/update
2025-11-03 update some schematic footprints
2025-11-06 update pcb from desktop
2025-11-10 update schematic from desktop
2025-11-10 fixed small things, push from laptop
2025-11-12 pcb v0.1 plus cad render for mech students
2025-11-20 laptop push of start of audio embedded code
2025-11-20 desktop new version of audio code to test on laptop
2025-11-20 untested, but working audio BL TX
2025-11-26 pcb updates from desktop with schematic fix
2025-11-26 extra commit to make sure i get everythin
2025-11-26 push from laptop to test code on desktop
2025-11-29 before saturday work
2025-11-30 update after lab session with gustav saturday
2025-12-01 finished PCB design and gerbers are in directory
2025-12-02 feedback from lawrence implemented in PCB design
2025-12-07 fixed .dxf 2d pcb for dinnis
2025-12-14 updated pcb code
2025-12-23 final push
2025-12-23 final push from desktop
2025-12-23 final push from laptop including converter scope pics
2026-01-20 cad files scent
2026-01-21 desktop push exam
